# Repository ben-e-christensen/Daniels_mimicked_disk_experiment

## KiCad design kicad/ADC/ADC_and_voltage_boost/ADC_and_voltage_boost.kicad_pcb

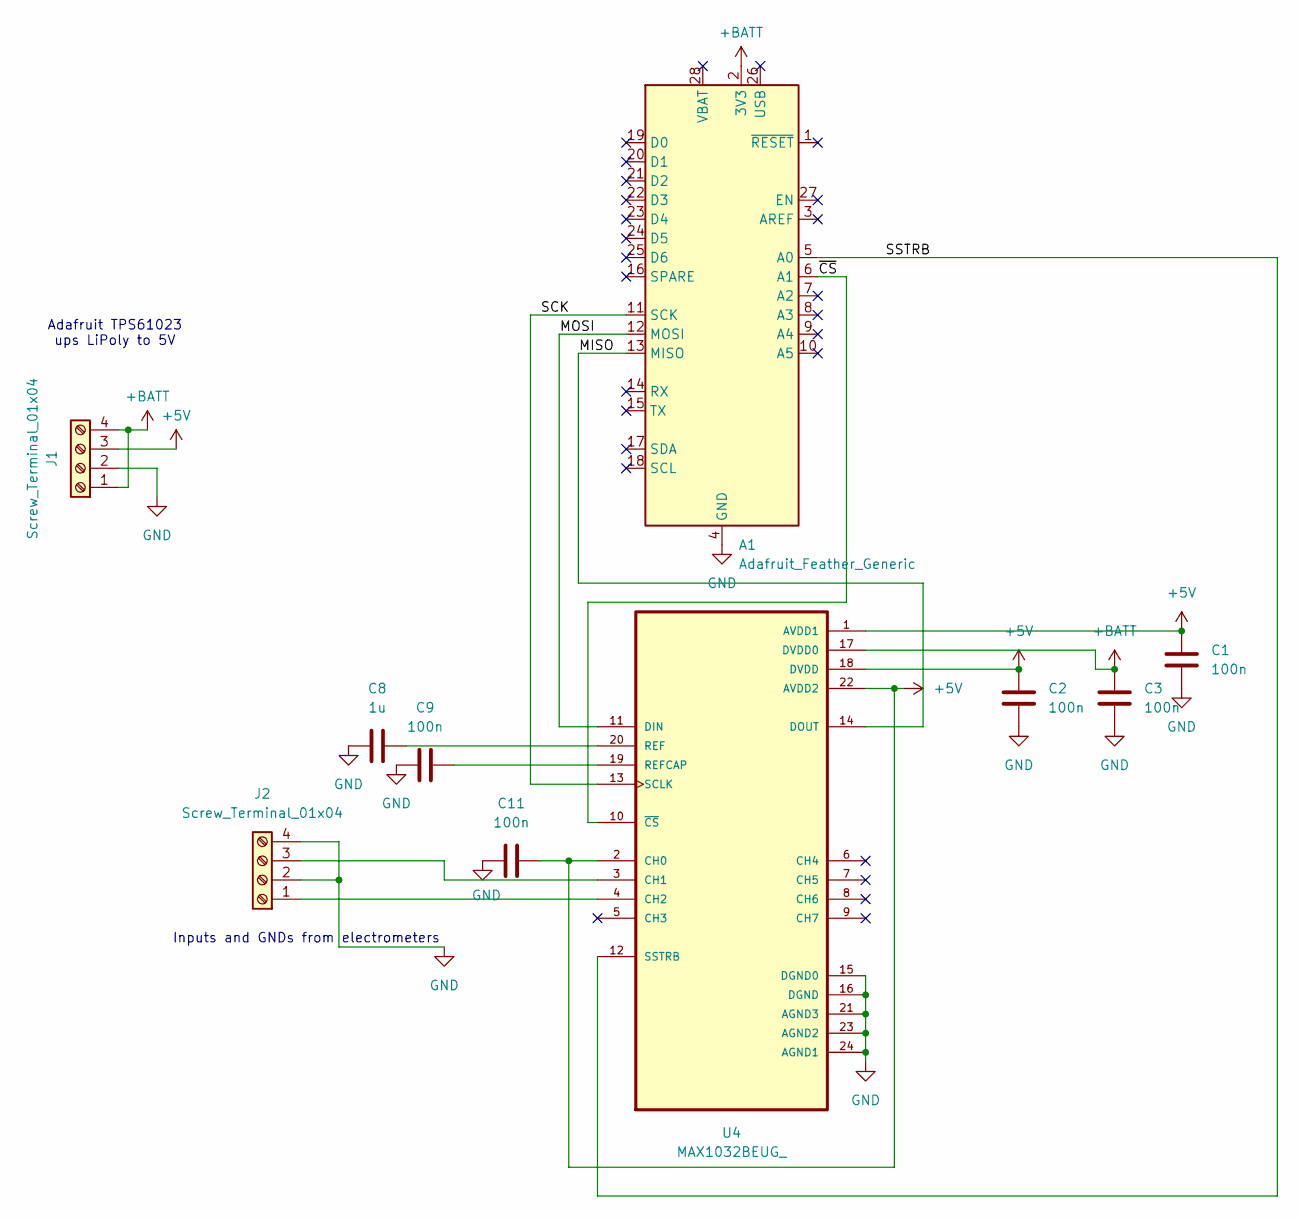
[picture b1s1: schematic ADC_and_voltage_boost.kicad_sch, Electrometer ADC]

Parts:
A1: Adafruit_Feather_Generic; Adafruit_Feather
C1, C2, C3, C9, C11: 100n; C_0805_2012Metric
C8: 1u; C_0805_2012Metric
J1, J2: Screw_Terminal_01x04; TerminalBlock_Phoenix_MPT-0,5-4-2.54_1x04_P2.54mm_Horizontal
U4: MAX1032BEUG_; SOP65P640X110-24N

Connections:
+5V: C1.1, C2.1, C11.2, J1.3, U4.1 (AVDD1), U4.2 (CH0), U4.18 (DVDD), U4.22 (AVDD2)
+BATT: A1.2 (3V3), C3.1, J1.1, J1.4, U4.17 (DVDD0)
/MISO: A1.13 (MISO), U4.14 (DOUT)
/MOSI: A1.12 (MOSI), U4.11 (DIN)
/SCK: A1.11 (SCK), U4.13 (SCLK)
/SSTRB: A1.5 (A0), U4.12 (SSTRB)
/~CS: A1.6 (A1), U4.10 (~CS)
GND: A1.4 (GND), C1.2, C2.2, C3.2, C8.1, C9.1, C11.1, J1.2, J2.2, J2.4, U4.15 (DGND0), U4.16 (DGND), U4.21 (AGND3), U4.23 (AGND2), U4.24 (AGND1)
unnamed: J2.1, U4.4 (CH2)
unnamed: J2.3, U4.3 (CH1)
unnamed: C8.2, U4.20 (REF)
unnamed: C9.2, U4.19 (REFCAP)

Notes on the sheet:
Adafruit TPS61023 ups LiPoly to 5V
Inputs and GNDs from electrometers

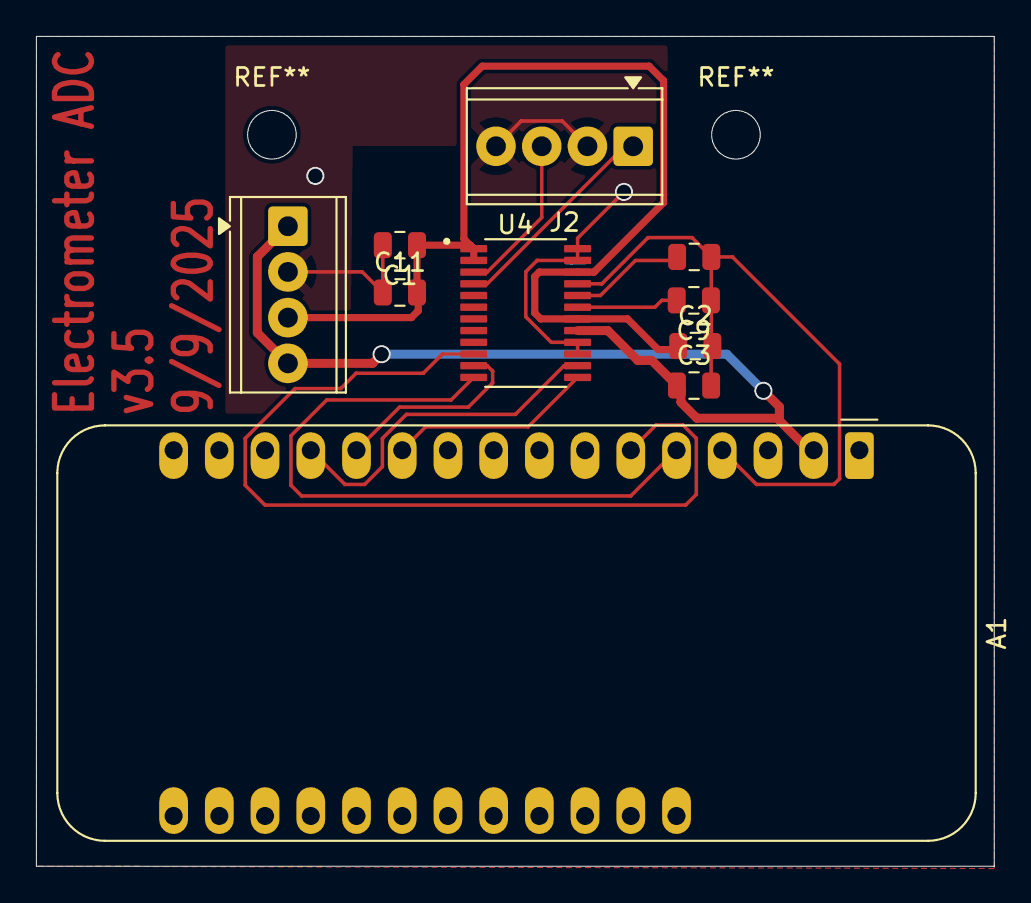
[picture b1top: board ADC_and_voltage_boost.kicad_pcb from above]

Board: 2 copper layers, 53.2 x 46.1 mm, 10 parts (0 on the bottom side), 12 nets.

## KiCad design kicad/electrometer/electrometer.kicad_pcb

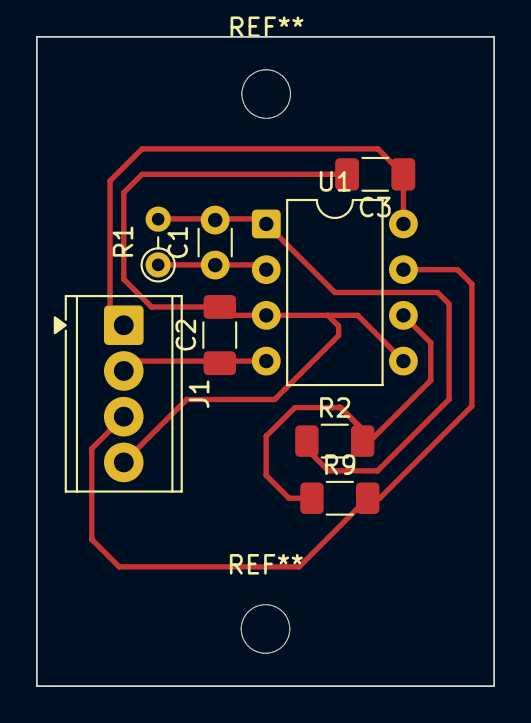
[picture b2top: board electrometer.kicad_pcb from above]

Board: 2 copper layers, 25.4 x 36.1 mm, 8 parts (0 on the bottom side), 7 nets.

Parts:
C1: 1e-03; C_Disc_D3.0mm_W1.6mm_P2.50mm
C2, C3: 1e-03; C_1206_3216Metric_Pad1.33x1.80mm_HandSolder
J1: Screw_Terminal_01x04; TerminalBlock_Phoenix_MPT-0,5-4-2.54_1x04_P2.54mm_Horizontal
R1: 1e+03; R_Axial_DIN0204_L3.6mm_D1.6mm_P2.54mm_Vertical
R2, R9: 1e+03; R_1206_3216Metric_Pad1.30x1.75mm_HandSolder
U1: LMC6082; DIP-8_W7.62mm

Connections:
+9V: C3.1, J1.1, U1.8 (V+)
-9V: C2.1, J1.2, U1.4 (V-)
GND: C2.2, C3.2, J1.4, U1.3 (+), U1.5 (+)
unnamed: C1.2, R1.2, R2.1, U1.1
unnamed: J1.3, R9.2, U1.7
unnamed: C1.1, R1.1, U1.2 (-)
unnamed: R2.2, R9.1, U1.6 (-)

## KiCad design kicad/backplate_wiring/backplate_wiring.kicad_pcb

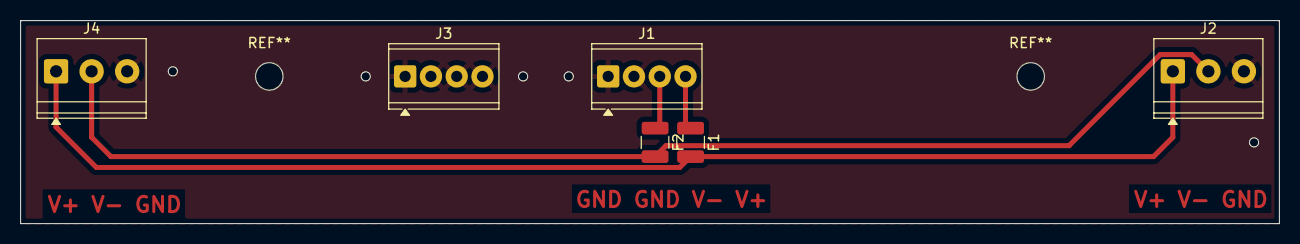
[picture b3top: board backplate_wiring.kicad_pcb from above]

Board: 2 copper layers, 124.0 x 20.0 mm, 6 parts (0 on the bottom side), 5 nets.

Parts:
F1, F2: Fuse; Fuse_1210_3225Metric
J1, J3: Screw_Terminal_01x04; TerminalBlock_Phoenix_MPT-0,5-4-2.54_1x04_P2.54mm_Horizontal
J2, J4: Screw_Terminal_01x03; TerminalBlock_Phoenix_PT-1,5-3-3.5-H_1x03_P3.50mm_Horizontal

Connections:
+BATT: F1.2, J2.1, J4.1
-BATT: F2.2, J2.2, J4.2
GND: J1.1, J1.2, J2.3, J3.1, J3.2, J3.3, J3.4, J4.3
unnamed: F2.1, J1.3
unnamed: F1.1, J1.4

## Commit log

2025-07-10 commiting all files from pi so can be more easily accessed from other devices
2025-07-14 camera feed and gui running at same time
2025-07-16 added threaded modules
2025-07-18 Added html file generation for easier data viewing. Lingerings of flask app are still present. May switch to it later, so leaving for now.
2025-07-19 refactored some code/removed old stuff/rearranged some files
2025-07-19 moved file
2025-07-24 seperated guis. Still need a bit more work on getting camera and other values on same window.
2025-07-29 test push
2025-07-30 updated pcb schematic. should fit back of disk now
2025-07-31 updated board
2025-08-03 BLE is making connection. Nothing past that. Rearranged a lil.
2025-08-09 moved around some kicad things. Added additional schematic for ADC and TPS60213
2025-08-10 finished schema/pcb
2025-08-11 updated pcb
2025-08-11 wireless commit
2025-08-14 removed old stuff
2025-08-14 low frequency comms are working well between pi and xiao
2025-08-15 committing before testing to pull arduino code onto another device. May need to rewrite all of this.
2025-08-15 deleted no longer used folder
2025-08-15 Added other .ino file
2025-08-15 adding tests
2025-08-15 analog fix?
2025-08-15 trying pulses at 500Hz
2025-08-16 adding new structuring
2025-08-16 working receiver codegit add -A
2025-08-16 added ino file
2025-08-16 good progress on the refactor so far.
2025-08-18 great start to the refactor
2025-08-18 more refactor and pushing it before I maybe break my pi
2025-08-22 finished ADC
2025-08-23 new kicad
2025-08-23 added another kicad board
2025-08-26 committing some adc board changes
2025-08-26 adding new backplate board
2025-08-26 added new kicad project to act as a compiler for laser jobs
2025-08-27 committing
2025-08-27 fixing board issues - kicad
2025-08-28 v3 for ADC up
2025-08-31 integrating things into main
2025-09-01 added oscilliscope view/camera to their own gui
2025-09-02 small refactor
2025-09-02 fixed small things
2025-09-02 a lot of buggy things fixed. Out sourced motor control to just the old gui. BLE taking too much in the loop. Motor was very janky when ble was running
2025-09-04 pretty much all things that need to be tracked are being tracked
2025-09-04 were haulin at 50FPS recorded!
2025-09-09 switched back to xiao on adc
